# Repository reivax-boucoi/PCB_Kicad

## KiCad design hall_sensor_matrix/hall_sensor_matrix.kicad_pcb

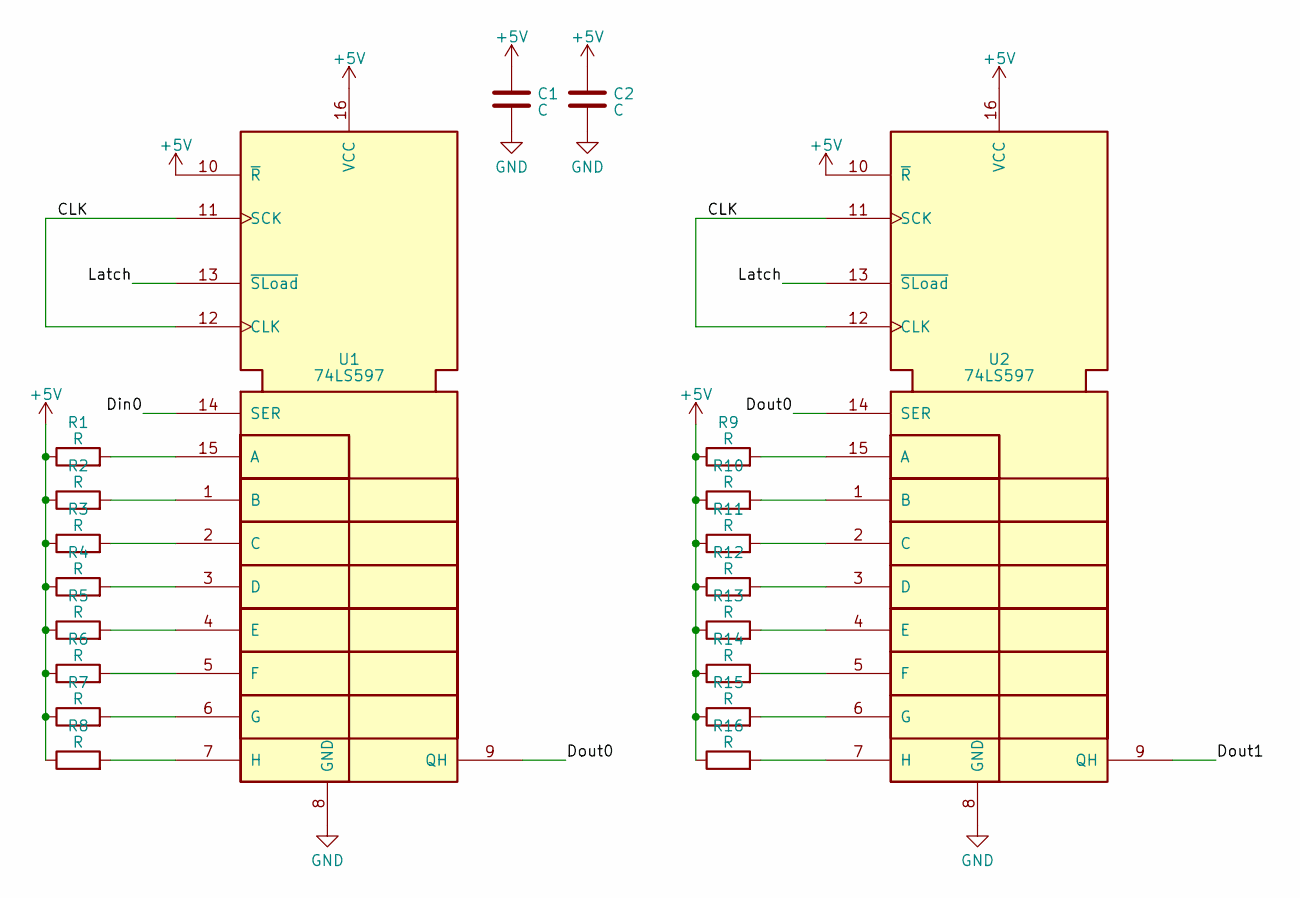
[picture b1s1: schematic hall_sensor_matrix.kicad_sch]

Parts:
C1, C2: C; C_Disc_D6.0mm_W2.5mm_P5.00mm
R1, R2, R3, R4, R5, R6, R7, R8, R9, R10, R11, R12, R13, R14, R15, R16: R; R_Axial_DIN0207_L6.3mm_D2.5mm_P2.54mm_Vertical
U1, U2: 74LS597; DIP-16_W7.62mm_LongPads

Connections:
+5V: C1.1, C2.1, R1.1, R2.1, R3.1, R4.1, R5.1, R6.1, R7.1, R8.1, R9.1, R10.1, R11.1, R12.1, R13.1, R14.1, R15.1, R16.1, U1.10 (~R), U1.16 (VCC), U2.10 (~R), U2.16 (VCC)
/CLK: U1.11 (SCK), U1.12 (CLK), U2.11 (SCK), U2.12 (CLK)
/Din0: U1.14 (SER)
/Dout0: U1.9 (QH), U2.14 (SER)
/Dout1: U2.9 (QH)
/Latch: U1.13 (~SLoad), U2.13 (~SLoad)
GND: C1.2, C2.2, U1.8 (GND), U2.8 (GND)
unnamed: R1.2, U1.15 (A)
unnamed: R2.2, U1.1 (B)
unnamed: R3.2, U1.2 (C)
unnamed: R4.2, U1.3 (D)
unnamed: R5.2, U1.4 (E)
unnamed: R6.2, U1.5 (F)
unnamed: R7.2, U1.6 (G)
unnamed: R8.2, U1.7 (H)
unnamed: R9.2, U2.15 (A)
unnamed: R10.2, U2.1 (B)
unnamed: R11.2, U2.2 (C)
unnamed: R12.2, U2.3 (D)
unnamed: R13.2, U2.4 (E)
unnamed: R14.2, U2.5 (F)
unnamed: R15.2, U2.6 (G)
unnamed: R16.2, U2.7 (H)

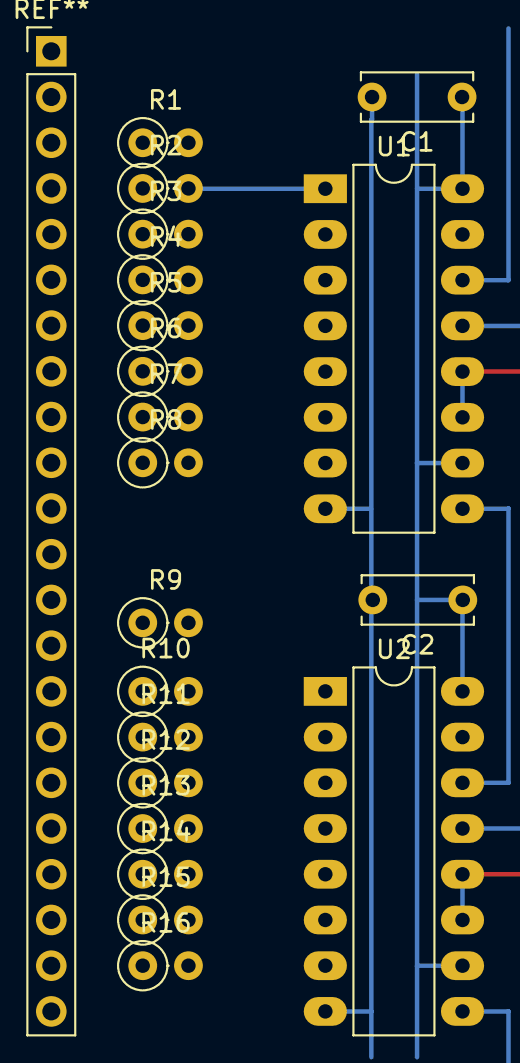
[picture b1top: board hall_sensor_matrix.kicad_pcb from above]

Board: 2 copper layers, 20 parts (0 on the bottom side), 21 nets.

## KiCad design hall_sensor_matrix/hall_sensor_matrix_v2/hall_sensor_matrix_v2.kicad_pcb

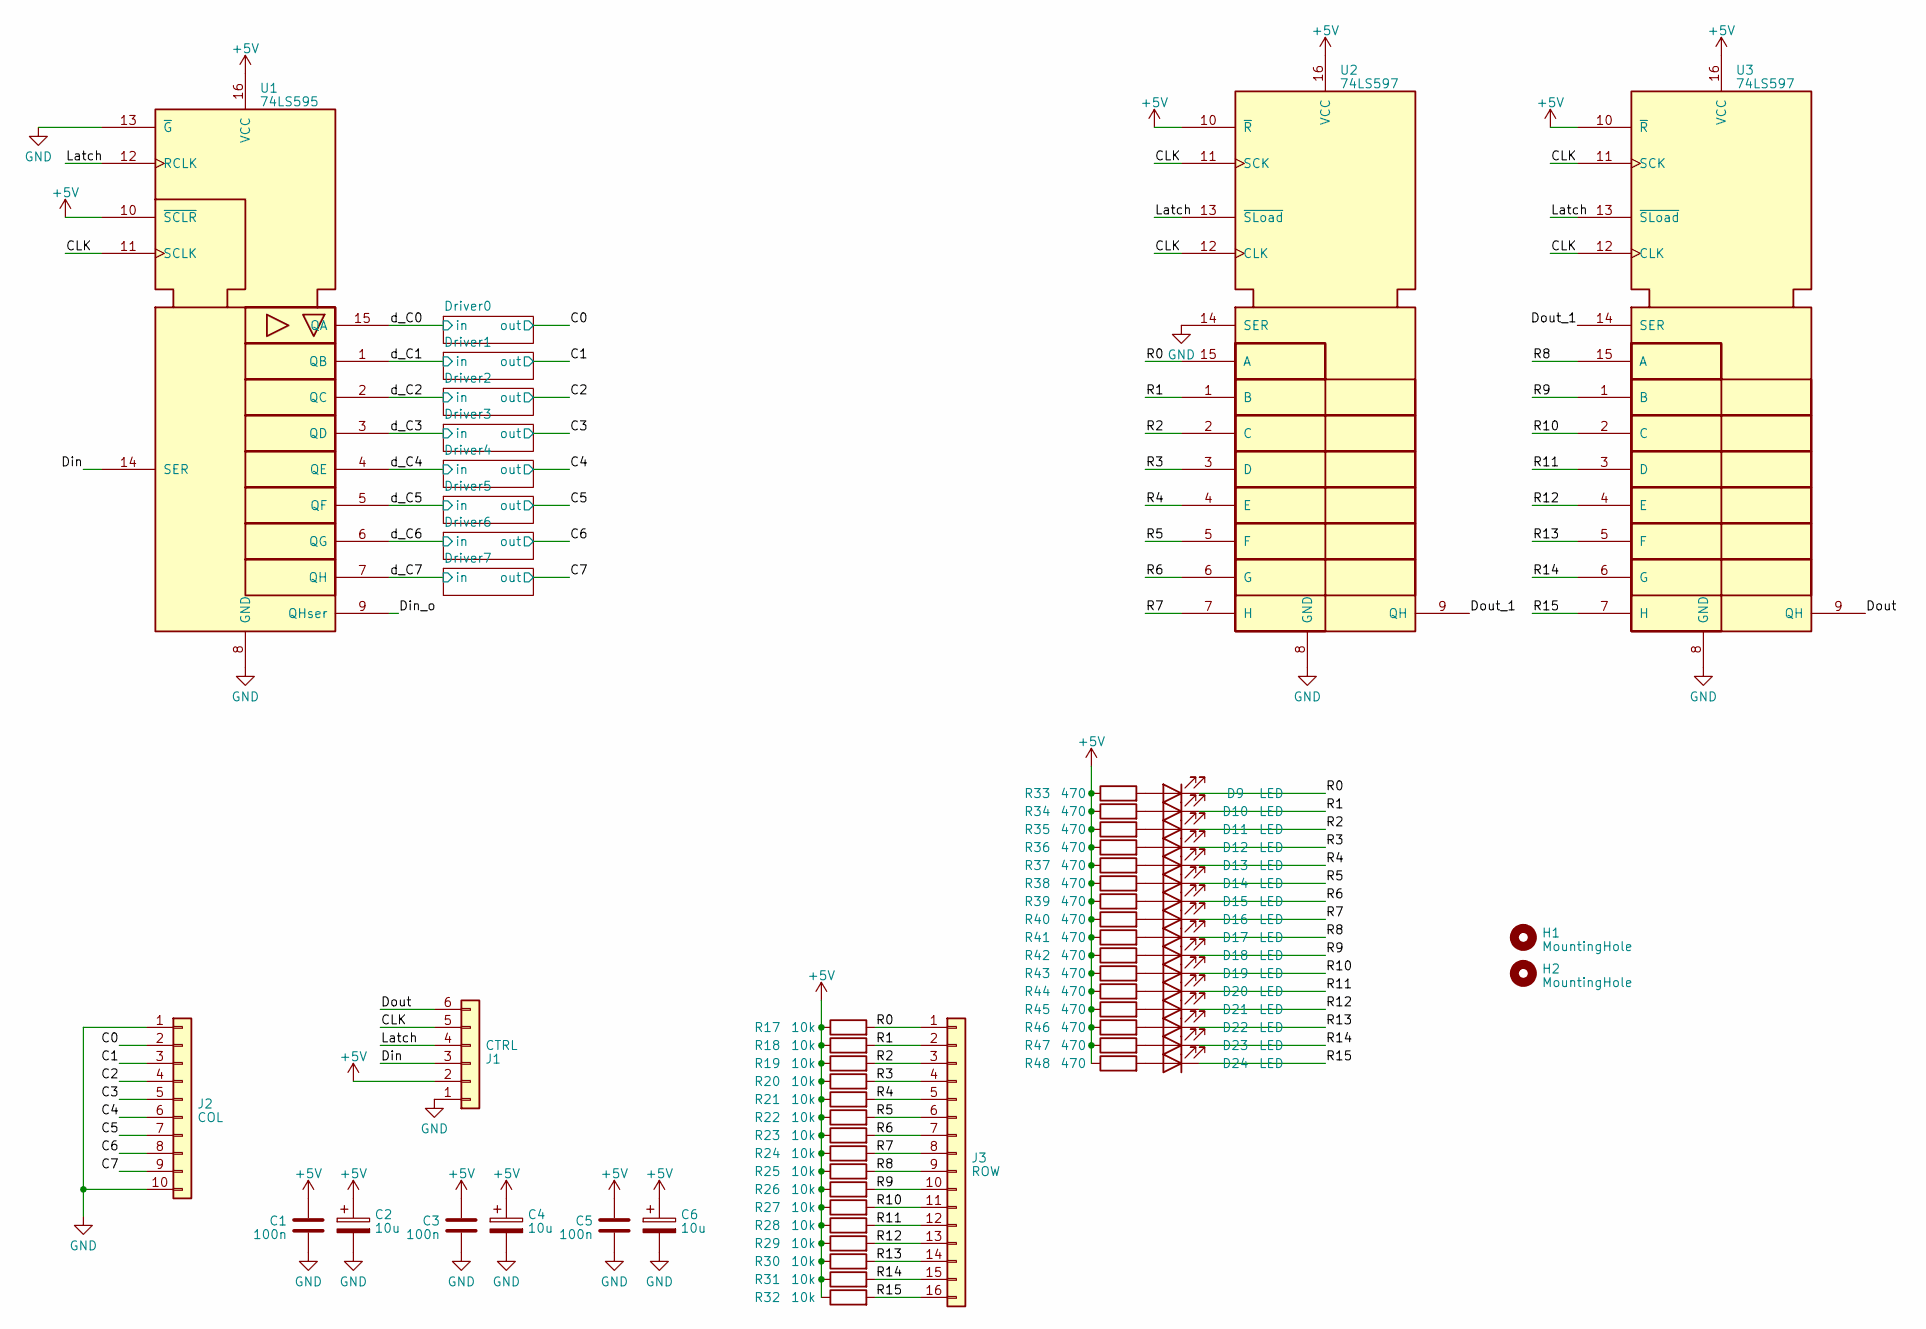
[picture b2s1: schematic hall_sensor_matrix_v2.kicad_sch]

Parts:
C1, C3, C5: 100n; C_0603_1608Metric_Pad1.08x0.95mm_HandSolder
C2, C4, C6: 10u; C_0805_2012Metric_Pad1.18x1.45mm_HandSolder
D9, D10, D11, D12, D13, D14, D15, D16, D17, D18, D19, D20, D21, D22, D23, D24: LED; LED_0603_1608Metric_Pad1.05x0.95mm_HandSolder
H1, H2: MountingHole; MountingHole_3.2mm_M3
J1: CTRL; PinSocket_1x06_P2.54mm_Horizontal
J2: COL; PinHeader_1x10_P2.54mm_Vertical
J3: ROW; PinHeader_1x16_P2.54mm_Vertical
R17, R18, R19, R20, R21, R22, R23, R24, R25, R26, R27, R28, R29, R30, R31, R32: 10k; R_0805_2012Metric
R33, R34, R35, R36, R37, R38, R39, R40, R41, R42, R43, R44, R45, R46, R47, R48: 470; R_0805_2012Metric
U1: 74LS595; DIP-16_W7.62mm_LongPads
U2, U3: 74LS597; DIP-16_W7.62mm_LongPads

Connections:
+5V: C1.1, C2.1, C3.1, C4.1, C5.1, C6.1, J1.2, R17.1, R18.1, R19.1, R20.1, R21.1, R22.1, R23.1, R24.1, R25.1, R26.1, R27.1, R28.1, R29.1, R30.1, R31.1, R32.1, R33.1, R34.1, R35.1, R36.1, R37.1, R38.1, R39.1, R40.1, R41.1, R42.1, R43.1, R44.1, R45.1, R46.1, R47.1, R48.1, U1.10 (~SCLR), U1.16 (VCC), U2.10 (~R), U2.16 (VCC), U3.10 (~R), U3.16 (VCC); also elsewhere on the board
/C0: J2.2; also elsewhere on the board
/C1: J2.3; also elsewhere on the board
/C2: J2.4; also elsewhere on the board
/C3: J2.5; also elsewhere on the board
/C4: J2.6; also elsewhere on the board
/C5: J2.7; also elsewhere on the board
/C6: J2.8; also elsewhere on the board
/C7: J2.9; also elsewhere on the board
/CLK: J1.5, U1.11 (SCLK), U2.11 (SCK), U2.12 (CLK), U3.11 (SCK), U3.12 (CLK)
/Din: J1.3, U1.14 (SER)
/Din_o: U1.9 (QHser)
/Dout: J1.6, U3.9 (QH)
/Dout_1: U2.9 (QH), U3.14 (SER)
/Latch: J1.4, U1.12 (RCLK), U2.13 (~SLoad), U3.13 (~SLoad)
/R0: D9.1 (K), J3.1, R17.2, U2.15 (A)
/R1: D10.1 (K), J3.2, R18.2, U2.1 (B)
/R2: D11.1 (K), J3.3, R19.2, U2.2 (C)
/R3: D12.1 (K), J3.4, R20.2, U2.3 (D)
/R4: D13.1 (K), J3.5, R21.2, U2.4 (E)
/R5: D14.1 (K), J3.6, R22.2, U2.5 (F)
/R6: D15.1 (K), J3.7, R23.2, U2.6 (G)
/R7: D16.1 (K), J3.8, R24.2, U2.7 (H)
/R8: D17.1 (K), J3.9, R25.2, U3.15 (A)
/R9: D18.1 (K), J3.10, R26.2, U3.1 (B)
/R10: D19.1 (K), J3.11, R27.2, U3.2 (C)
/R11: D20.1 (K), J3.12, R28.2, U3.3 (D)
/R12: D21.1 (K), J3.13, R29.2, U3.4 (E)
/R13: D22.1 (K), J3.14, R30.2, U3.5 (F)
/R14: D23.1 (K), J3.15, R31.2, U3.6 (G)
/R15: D24.1 (K), J3.16, R32.2, U3.7 (H)
/d_C0: U1.15 (QA); also elsewhere on the board
/d_C1: U1.1 (QB); also elsewhere on the board
/d_C2: U1.2 (QC); also elsewhere on the board
/d_C3: U1.3 (QD); also elsewhere on the board
/d_C4: U1.4 (QE); also elsewhere on the board
/d_C5: U1.5 (QF); also elsewhere on the board
/d_C6: U1.6 (QG); also elsewhere on the board
/d_C7: U1.7 (QH); also elsewhere on the board
GND: C1.2, C2.2, C3.2, C4.2, C5.2, C6.2, J1.1, J2.1, J2.10, U1.8 (GND), U1.13 (~G), U2.8 (GND), U2.14 (SER), U3.8 (GND); also elsewhere on the board
unnamed: D9.2 (A), R33.2
unnamed: D10.2 (A), R34.2
unnamed: D11.2 (A), R35.2
unnamed: D12.2 (A), R36.2
unnamed: D13.2 (A), R37.2
unnamed: D14.2 (A), R38.2
unnamed: D15.2 (A), R39.2
unnamed: D16.2 (A), R40.2
unnamed: D17.2 (A), R41.2
unnamed: D18.2 (A), R42.2
unnamed: D19.2 (A), R43.2
unnamed: D20.2 (A), R44.2
unnamed: D21.2 (A), R45.2
unnamed: D22.2 (A), R46.2
unnamed: D23.2 (A), R47.2
unnamed: D24.2 (A), R48.2

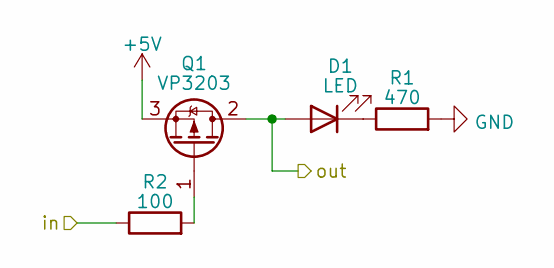
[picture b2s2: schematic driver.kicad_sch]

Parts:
D1: LED; LED_0603_1608Metric_Pad1.05x0.95mm_HandSolder
Q1: VP3203; SOT-89-3
R1: 470; R_0805_2012Metric
R2: 100; R_0805_2012Metric

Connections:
+5V: Q1.3 (S); also elsewhere on the board
/C0: D1.2 (A), Q1.2 (D); also elsewhere on the board
/d_C0: R2.1; also elsewhere on the board
GND: R1.2; also elsewhere on the board
unnamed: D1.1 (K), R1.1
unnamed: Q1.1 (G), R2.2

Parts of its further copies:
D2, D3, D4, D5, D6, D7, D8: LED; LED_0603_1608Metric_Pad1.05x0.95mm_HandSolder
Q2, Q3, Q4, Q5, Q6, Q7, Q8: VP3203; SOT-89-3
R3, R5, R7, R9, R11, R13, R15: 470; R_0805_2012Metric
R4, R6, R8, R10, R12, R14, R16: 100; R_0805_2012Metric

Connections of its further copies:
+5V: Q2.3 (S), Q3.3 (S), Q4.3 (S), Q5.3 (S), Q6.3 (S), Q7.3 (S), Q8.3 (S); also elsewhere on the board
/C1: D2.2 (A), Q2.2 (D); also elsewhere on the board
/C2: D3.2 (A), Q3.2 (D); also elsewhere on the board
/C3: D4.2 (A), Q4.2 (D); also elsewhere on the board
/C4: D5.2 (A), Q5.2 (D); also elsewhere on the board
/C5: D6.2 (A), Q6.2 (D); also elsewhere on the board
/C6: D7.2 (A), Q7.2 (D); also elsewhere on the board
/C7: D8.2 (A), Q8.2 (D); also elsewhere on the board
/d_C1: R4.1; also elsewhere on the board
/d_C2: R6.1; also elsewhere on the board
/d_C3: R8.1; also elsewhere on the board
/d_C4: R10.1; also elsewhere on the board
/d_C5: R12.1; also elsewhere on the board
/d_C6: R14.1; also elsewhere on the board
/d_C7: R16.1; also elsewhere on the board
GND: R3.2, R5.2, R7.2, R9.2, R11.2, R13.2, R15.2; also elsewhere on the board
unnamed: D2.1 (K), R3.1
unnamed: D3.1 (K), R5.1
unnamed: D4.1 (K), R7.1
unnamed: D5.1 (K), R9.1
unnamed: D6.1 (K), R11.1
unnamed: D7.1 (K), R13.1
unnamed: D8.1 (K), R15.1
unnamed: Q2.1 (G), R4.2
unnamed: Q3.1 (G), R6.2
unnamed: Q4.1 (G), R8.2
unnamed: Q5.1 (G), R10.2
unnamed: Q6.1 (G), R12.2
unnamed: Q7.1 (G), R14.2
unnamed: Q8.1 (G), R16.2

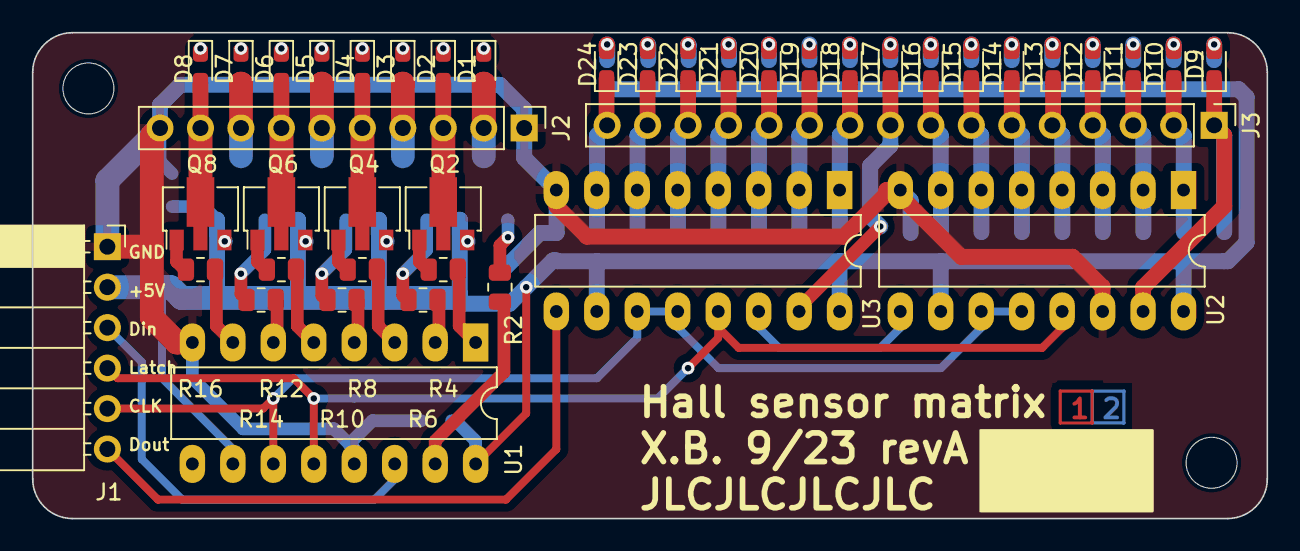
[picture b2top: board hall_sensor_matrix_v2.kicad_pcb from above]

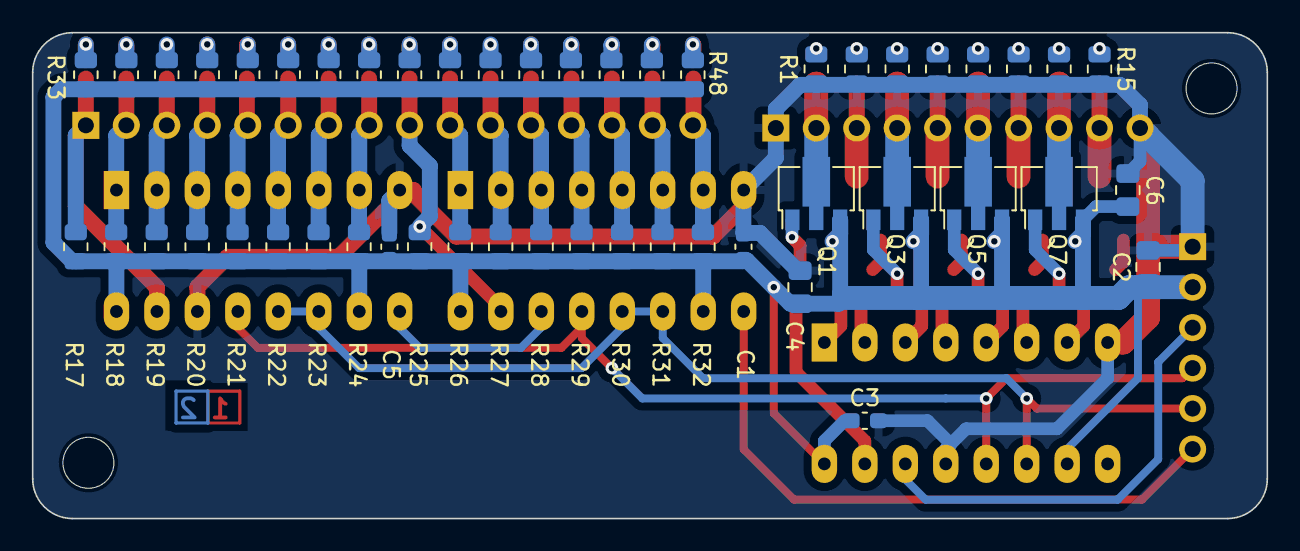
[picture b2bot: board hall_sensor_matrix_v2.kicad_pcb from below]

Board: 2 copper layers, 77.5 x 30.5 mm, 94 parts (50 on the bottom side), 71 nets.

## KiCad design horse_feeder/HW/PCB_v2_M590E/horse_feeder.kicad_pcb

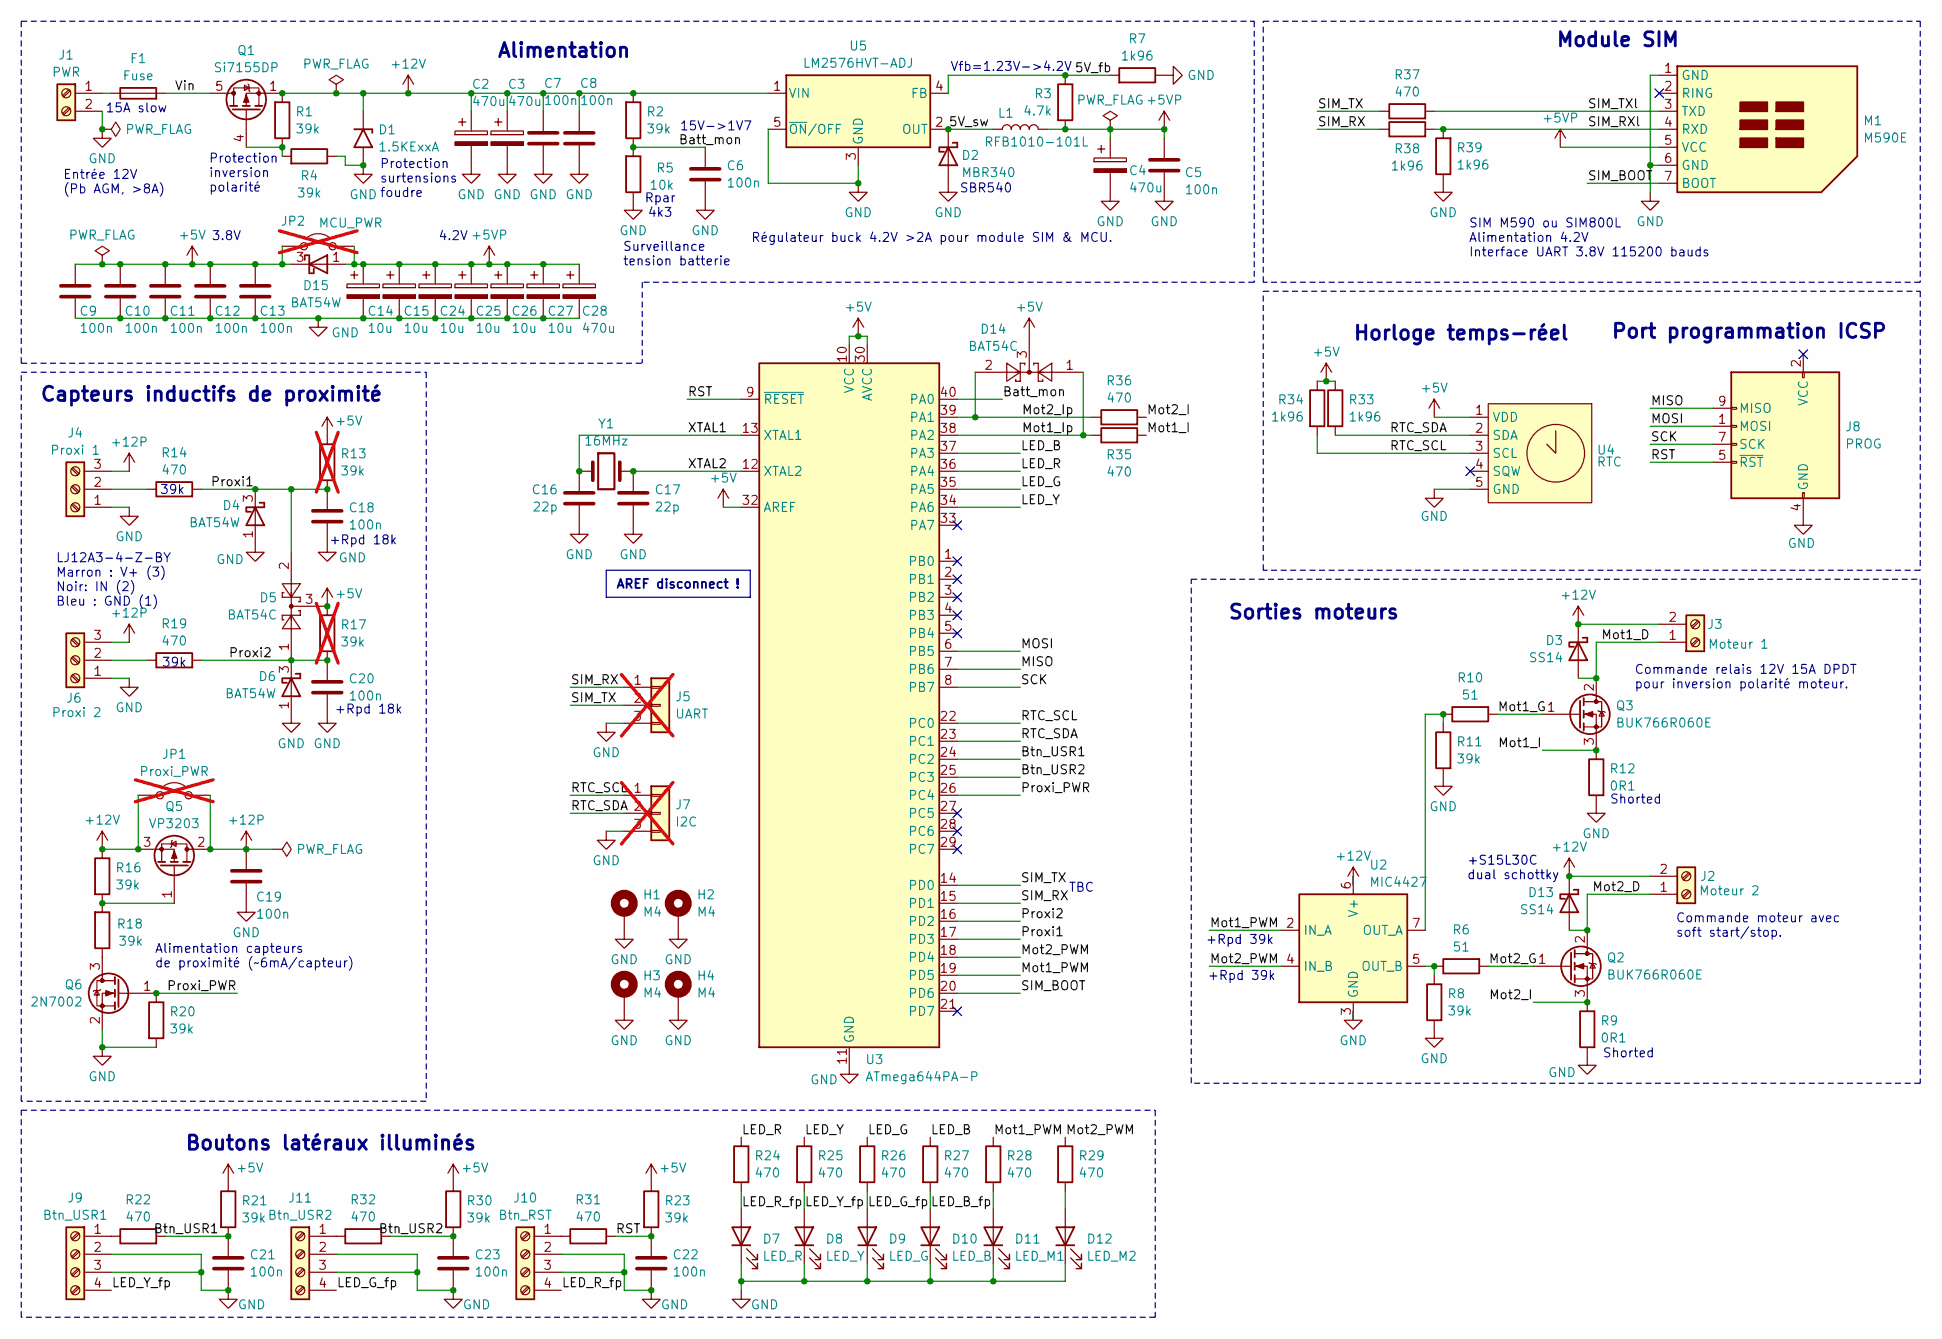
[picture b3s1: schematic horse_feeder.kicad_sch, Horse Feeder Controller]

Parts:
C2, C3, C4, C28: 470u; CP_Radial_D12.5mm_P5.00mm
C5, C6, C7, C8, C9, C10, C11, C12, C13, C18, C19, C20, C21, C22, C23: 100n; C_0805_2012Metric_Pad1.18x1.45mm_HandSolder
C14, C15, C24, C25, C26, C27: 10u; C_0805_2012Metric_Pad1.18x1.45mm_HandSolder
C16, C17: 22p; C_0603_1608Metric_Pad1.08x0.95mm_HandSolder
D1: 1.5KExxA; D_DO-201AE_P15.24mm_Horizontal
D2: MBR340; D_DO-201AD_P15.24mm_Horizontal
D3, D13: SS14; D_SMA
D4, D6, D15: BAT54W; SOT-23
D5, D14: BAT54C; SOT-23
D7: LED_R; LED_D5.0mm
D8: LED_Y; LED_D5.0mm
D9: LED_G; LED_D5.0mm
D10: LED_B; LED_D5.0mm
D11: LED_M1; LED_0805_2012Metric
D12: LED_M2; LED_0805_2012Metric
F1: Fuse; Fuseholder_Cylinder-5x20mm_Stelvio-Kontek_PTF78_Horizontal_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
H1, H2, H3, H4: M4; MountingHole_4.3mm_M4_Pad_Via
J1: PWR; TerminalBlock_bornier-2_P5.08mm
J2: Moteur 2; TerminalBlock_bornier-2_P5.08mm
J3: Moteur 1; TerminalBlock_bornier-2_P5.08mm
J4: Proxi 1; 282834-3
J5: UART; PinHeader_1x03_P2.54mm_Vertical; not fitted
J6: Proxi 2; 282834-3
J7: I2C; PinHeader_1x03_P2.54mm_Vertical; not fitted
J8: PROG; IDC-Header_2x05_P2.54mm_Vertical
J9: Btn_USR1; 282834-4
J10: Btn_RST; 282834-4
J11: Btn_USR2; 282834-4
JP1: Proxi_PWR; SolderJumper-2_P1.3mm_Open_RoundedPad1.0x1.5mm; not fitted
JP2: MCU_PWR; SolderJumper-2_P1.3mm_Open_RoundedPad1.0x1.5mm; not fitted
L1: RFB1010-101L; RFB1010
M1: M590E
Q1: Si7155DP; PowerPAK_SO-8_Single
Q2, Q3: BUK766R060E; TO-263-2
Q5: VP3203; SOT-89-3_Handsoldering
Q6: 2N7002; SOT-23
R1, R2, R4, R8, R11, R16, R18, R20, R21, R23, R30: 39k; R_0805_2012Metric_Pad1.20x1.40mm_HandSolder
R3: 4.7k; R_0805_2012Metric_Pad1.20x1.40mm_HandSolder
R5: 10k; R_0805_2012Metric_Pad1.20x1.40mm_HandSolder
R6, R10: 51; R_0805_2012Metric_Pad1.20x1.40mm_HandSolder
R7, R33, R34, R38, R39: 1k96; R_0805_2012Metric_Pad1.20x1.40mm_HandSolder
R9, R12: 0R1; R_1210_3225Metric_Pad1.30x2.65mm_HandSolder
R13, R17: 39k; R_0805_2012Metric_Pad1.20x1.40mm_HandSolder; not fitted
R14, R19, R22, R24, R25, R26, R27, R28, R29, R31, R32, R35, R36, R37: 470; R_0805_2012Metric_Pad1.20x1.40mm_HandSolder
U2: MIC4427; DIP-8_W7.62mm_Socket_LongPads
U3: ATmega644PA-P; DIP-40_W15.24mm
U4: RTC; DS3231_RTC_module
U5: LM2576HVT-ADJ; TO-220-5_Vertical
Y1: 16MHz; Crystal_SMD_HC49-SD

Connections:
+5V: C9.1, C10.1, C11.1, C12.1, C13.1, D5.3, D14.3, D15.3 (K), JP2.1 (A), R13.1, R17.1, R21.1, R23.1, R30.1, R33.1, R34.1, U3.10 (VCC), U3.30 (AVCC), U3.32 (AREF), U4.1 (VDD)
+5VP: C4.1, C5.1, C14.1, C15.1, C24.1, C25.1, C26.1, C27.1, C28.1, D15.1 (A), JP2.2 (B), L1.2, M1.5 (VCC), R3.2
+12P: C19.1, J4.3, J6.3, JP1.2 (B), Q5.2 (D)
+12V: C2.1, C3.1, C7.1, C8.1, D1.1 (A1), D3.1 (K), D13.1 (K), J2.2, J3.2, JP1.1 (A), Q1.1 (S), Q1.2 (S), Q1.3 (S), Q5.3 (S), R1.2, R2.2, R16.1, U2.6 (V+), U5.1 (VIN)
/5V_fb: R3.1, R7.2, U5.4 (FB)
/5V_sw: D2.1 (K), L1.1, U5.2 (OUT)
/Batt_mon: C6.1, R2.1, R5.2, U3.40 (PA0)
/Btn_USR1: C21.1, R21.2, R22.2, U3.24 (PC2)
/Btn_USR2: C23.1, R30.2, R32.2, U3.25 (PC3)
/LED_B: R27.1, U3.37 (PA3)
/LED_B_fp: D10.2 (A), R27.2
/LED_G: R26.1, U3.35 (PA5)
/LED_G_fp: D9.2 (A), J11.4, R26.2
/LED_R: R24.1, U3.36 (PA4)
/LED_R_fp: D7.2 (A), J10.4, R24.2
/LED_Y: R25.1, U3.34 (PA6)
/LED_Y_fp: D8.2 (A), J9.4, R25.2
/MISO: J8.9 (MISO), U3.7 (PB6)
/MOSI: J8.1 (MOSI), U3.6 (PB5)
/Mot1_D: D3.2 (A), J3.1, Q3.2 (D)
/Mot1_G: Q3.1 (G), R10.2
/Mot1_I: Q3.3 (S), R12.1, R35.2
/Mot1_Ip: D14.1, R35.1, U3.38 (PA2)
/Mot1_PWM: R28.1, U2.2 (IN_A), U3.19 (PD5)
/Mot2_D: D13.2 (A), J2.1, Q2.2 (D)
/Mot2_G: Q2.1 (G), R6.2
/Mot2_I: Q2.3 (S), R9.1, R36.2
/Mot2_Ip: D14.2, R36.1, U3.39 (PA1)
/Mot2_PWM: R29.1, U2.4 (IN_B), U3.18 (PD4)
/Proxi1: C18.1, D4.3 (K), D5.2, R13.2, R14.2, U3.17 (PD3)
/Proxi2: C20.1, D5.1, D6.3 (K), R17.2, R19.2, U3.16 (PD2)
/Proxi_PWR: Q6.1 (G), R20.1, U3.26 (PC4)
/RST: C22.1, J8.5 (~RST), R23.2, R31.2, U3.9 (~RESET)
/RTC_SCL: J7.1, R34.2, U3.22 (PC0), U4.3 (SCL)
/RTC_SDA: J7.2, R33.2, U3.23 (PC1), U4.2 (SDA)
/SCK: J8.7 (SCK), U3.8 (PB7)
/SIM_BOOT: M1.7 (BOOT), U3.20 (PD6)
/SIM_RX: J5.1, R38.1, U3.15 (PD1)
/SIM_RXl: M1.4 (RXD), R38.2, R39.2
/SIM_TX: J5.2, R37.1, U3.14 (PD0)
/SIM_TXl: M1.3 (TXD), R37.2
/Vin: F1.2, Q1.5 (D)
/XTAL1: C16.1, U3.13 (XTAL1), Y1.1
/XTAL2: C17.1, U3.12 (XTAL2), Y1.2
GND: C2.2, C3.2, C4.2, C5.2, C6.2, C7.2, C8.2, C9.2, C10.2, C11.2, C12.2, C13.2, C14.2, C15.2, C16.2, C17.2, C18.2, C19.2, C20.2, C21.2, C22.2, C23.2, C24.2, C25.2, C26.2, C27.2, C28.2, D1.2 (A2), D2.2 (A), D4.1 (A), D6.1 (A), D7.1 (K), D8.1 (K), D9.1 (K), D10.1 (K), D11.1 (K), D12.1 (K), H1.1, H2.1, H3.1, H4.1, J1.2, J4.1, J5.3, J6.1, J7.3, J8.4 (GND), J8.6 (GND), J8.8 (GND), J8.10 (GND), J9.2, J9.3, J10.2, J10.3, J11.2, J11.3, M1.1 (GND), M1.6 (GND), Q6.2 (S), R4.1, R5.1, R7.1, R8.2, R9.2, R11.2, R12.2, R20.2, R39.1, U2.3 (GND), U3.11 (GND), U3.31 (GND), U4.5 (GND), U5.3 (GND), U5.5 (~ON/OFF)
unnamed: D11.2 (A), R28.2
unnamed: D12.2 (A), R29.2
unnamed: F1.1, J1.1
unnamed: J4.2, R14.1
unnamed: J6.2, R19.1
unnamed: J9.1, R22.1
unnamed: J10.1, R31.1
unnamed: J11.1, R32.1
unnamed: Q1.4 (G), R1.1, R4.2
unnamed: Q5.1 (G), R16.2, R18.2
unnamed: Q6.3 (D), R18.1
unnamed: R10.1, R11.1, U2.7 (OUT_A)
unnamed: R6.1, R8.1, U2.5 (OUT_B)

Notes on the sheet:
AREF disconnect !
LJ12A3-4-Z-BY Marron : V+ (3) Noir: IN (2) Bleu : GND (1)
Boutons latéraux illuminés
15V->1V7
Surveillance tension batterie
15A slow
Capteurs inductifs de proximité
Protection inversion polarité
+Rpd 39k
+Rpd 18k
4.2V
Sorties moteurs
Module SIM
3.8V
39k
Protection surtensions foudre
Port programmation ICSP
Entrée 12V (Pb AGM, >8A)
Shorted
Horloge temps-réel
TBC
+S15L30C dual schottky
Régulateur buck 4.2V >2A pour module SIM & MCU.
Alimentation
Commande moteur avec soft start/stop.
SIM M590 ou SIM800L Alimentation 4.2V Interface UART 3.8V 115200 bauds
Commande relais 12V 15A DPDT pour inversion polarité moteur.
Vfb=1.23V->4.2V
Rpar 4k3
SBR540
Alimentation capteurs de proximité (~6mA/capteur)

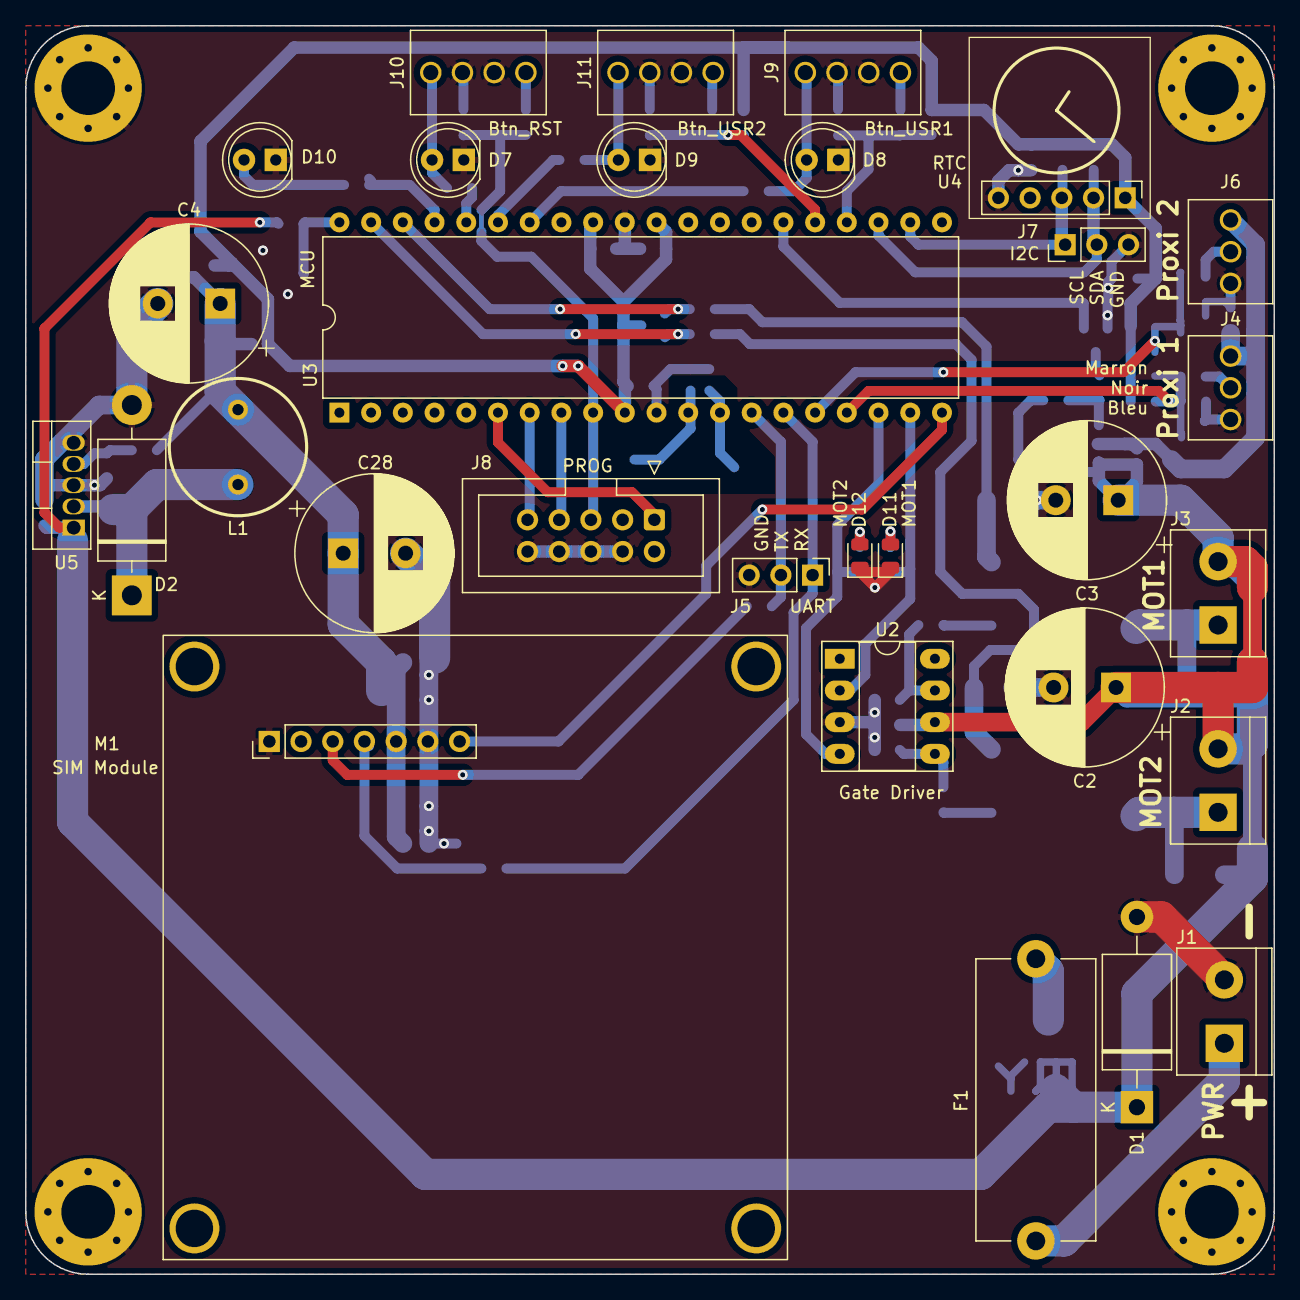
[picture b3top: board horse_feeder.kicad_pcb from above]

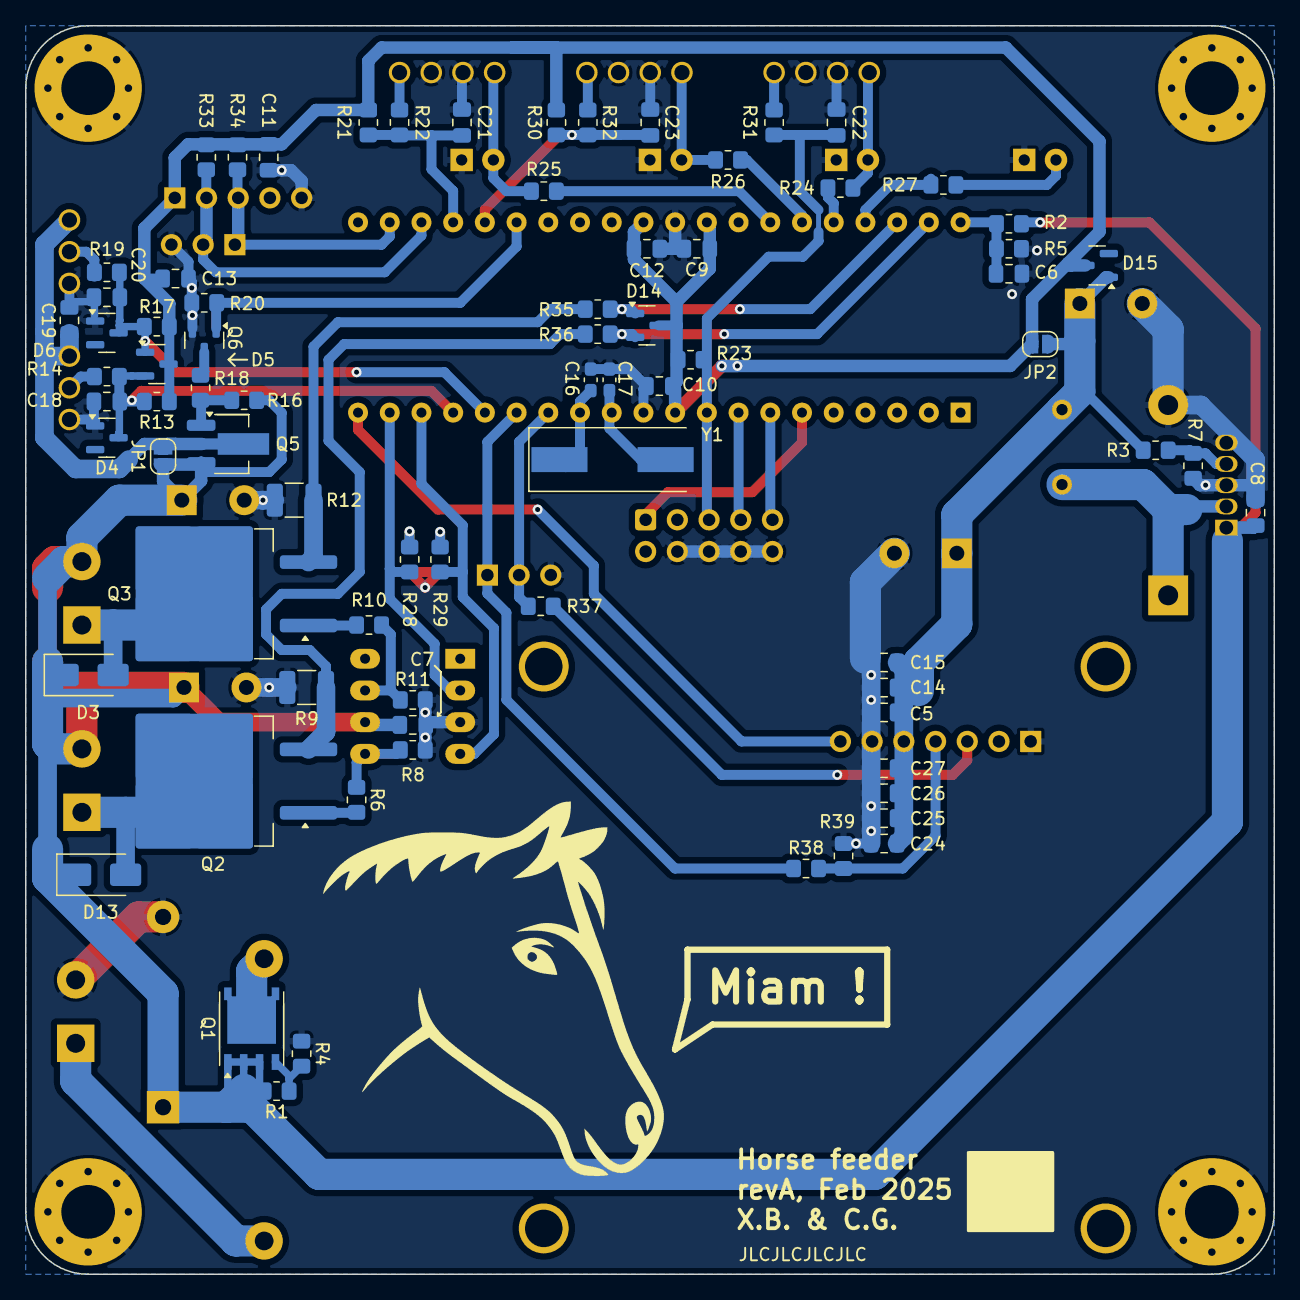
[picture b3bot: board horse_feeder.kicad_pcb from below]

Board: 2 copper layers, 100.0 x 100.0 mm, 110 parts (76 on the bottom side), 58 nets.
